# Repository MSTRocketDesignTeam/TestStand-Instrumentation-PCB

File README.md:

# Purpose
This repo will hold all of the relevant design files for the Rocket Design Team's Test Stand.

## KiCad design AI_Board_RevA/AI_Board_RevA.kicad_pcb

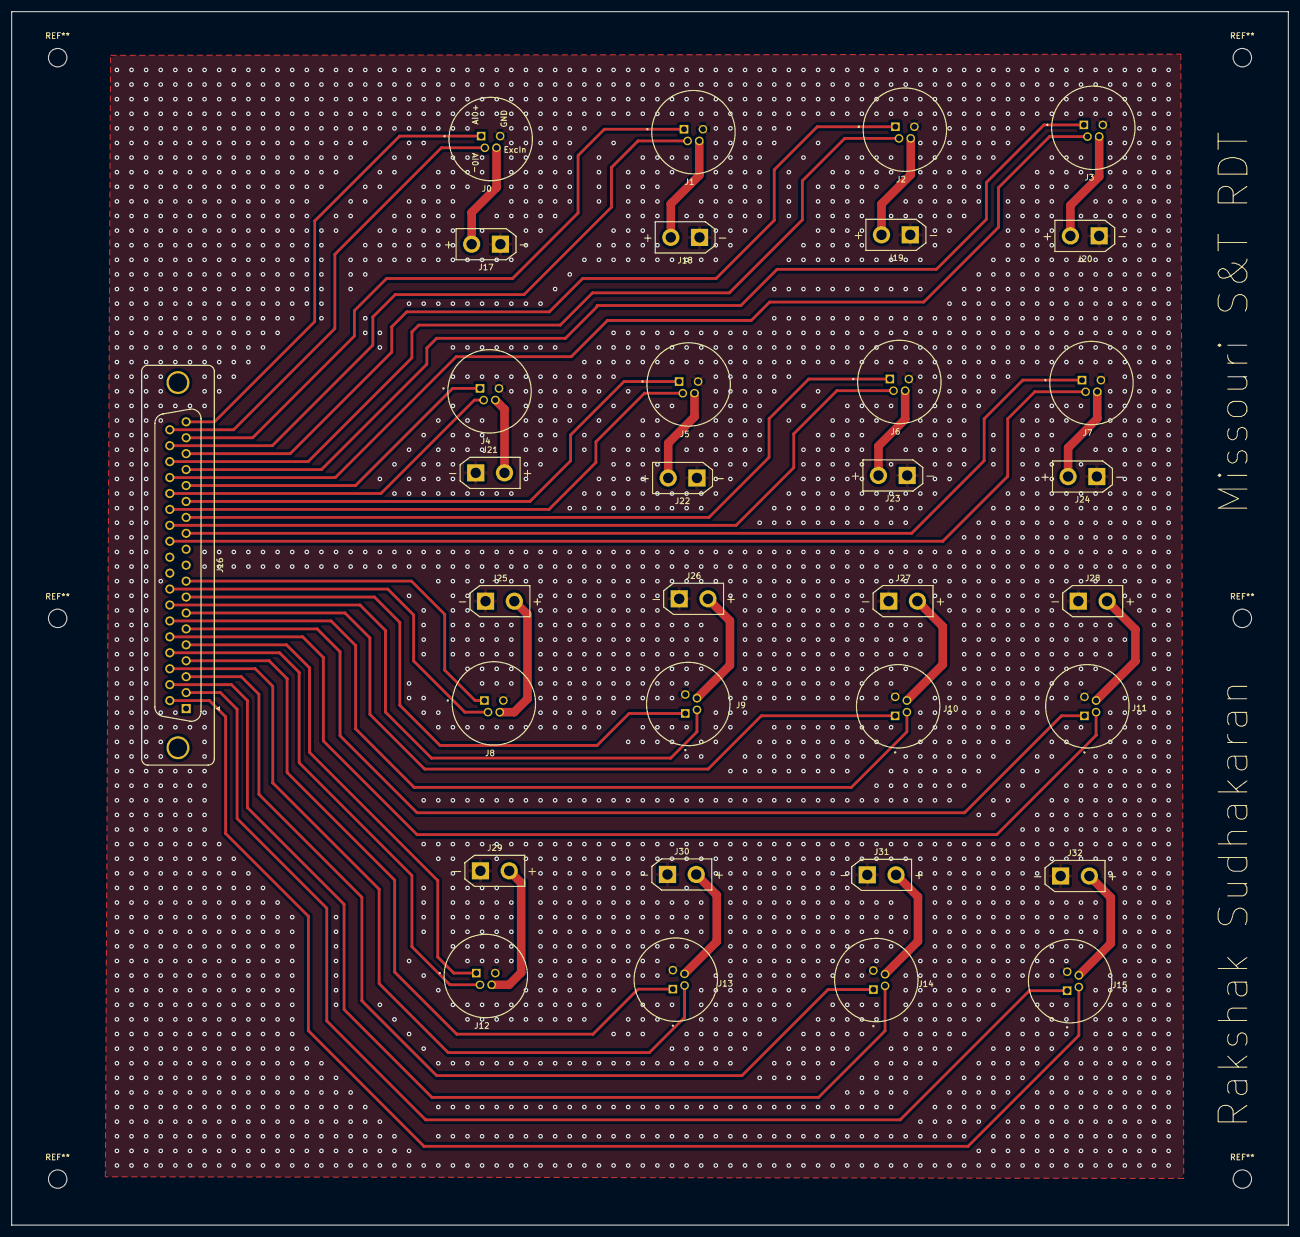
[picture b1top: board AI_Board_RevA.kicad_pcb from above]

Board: 2 copper layers, 222.0 x 211.0 mm, 33 parts (0 on the bottom side), 50 nets.

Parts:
J0, J1, J2, J3, J4, J5, J6, J7, J8, J9, J10, J11, J12, J13, J14, J15: Conn_01x04; TENSILITY_54-00278
J16: DB37_Female; DSUB-37_Female_Vertical_P2.77x2.84mm_MountingHoles
J17, J18, J19, J20, J21, J22, J23, J24, J25, J26, J27, J28, J29, J30, J31, J32: Conn_01x02; AMASS_XT30UPB-F_1x02_P5.0mm_Vertical

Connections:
/AI0+: J0.1, J16.19
/AI0-: J0.2, J16.37
/AI1+: J1.1, J16.18
/AI1-: J1.2, J16.36
/AI2+: J2.1, J16.17
/AI2-: J2.2, J16.35
/AI3+: J3.1, J16.16
/AI3-: J3.2, J16.34
/AI4+: J4.1, J16.15
/AI4-: J4.2, J16.33
/AI5+: J5.1, J16.14
/AI5-: J5.2, J16.32
/AI6+: J6.1, J16.13
/AI6-: J6.2, J16.31
/AI7+: J7.1, J16.12
/AI7-: J7.2, J16.30
/AI8+: J8.1, J16.9
/AI8-: J8.2, J16.27
/AI9+: J9.1, J16.8
/AI9-: J9.2, J16.26
/AI10+: J10.1, J16.7
/AI10-: J10.2, J16.25
/AI11+: J11.1, J16.6
/AI11-: J11.2, J16.24
/AI12+: J12.1, J16.5
/AI12-: J12.2, J16.23
/AI13+: J13.1, J16.4
/AI13-: J13.2, J16.22
/AI14+: J14.1, J16.3
/AI14-: J14.2, J16.21
/AI15+: J15.1, J16.2
/AI15-: J15.2, J16.20
/COM: J16.10, J16.11, J16.28, J16.29
GND: J0.3, J1.3, J2.3, J3.3, J4.3, J5.3, J6.3, J7.3, J8.3, J9.3, J10.3, J11.3, J12.3, J13.3, J14.3, J15.3, J17.1, J18.1, J19.1, J20.1, J21.1, J22.1, J23.1, J24.1, J25.1, J26.1, J27.1, J28.1, J29.1, J30.1, J31.1, J32.1
unnamed: J0.4, J17.2
unnamed: J1.4, J18.2
unnamed: J10.4, J27.2
unnamed: J11.4, J28.2
unnamed: J12.4, J29.2
unnamed: J13.4, J30.2
unnamed: J14.4, J31.2
unnamed: J15.4, J32.2
unnamed: J2.4, J19.2
unnamed: J3.4, J20.2
unnamed: J4.4, J21.2
unnamed: J5.4, J22.2
unnamed: J6.4, J23.2
unnamed: J7.4, J24.2
unnamed: J8.4, J25.2
unnamed: J9.4, J26.2

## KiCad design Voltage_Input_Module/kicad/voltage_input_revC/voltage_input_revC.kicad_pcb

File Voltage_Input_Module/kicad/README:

Save the main kicad project here.

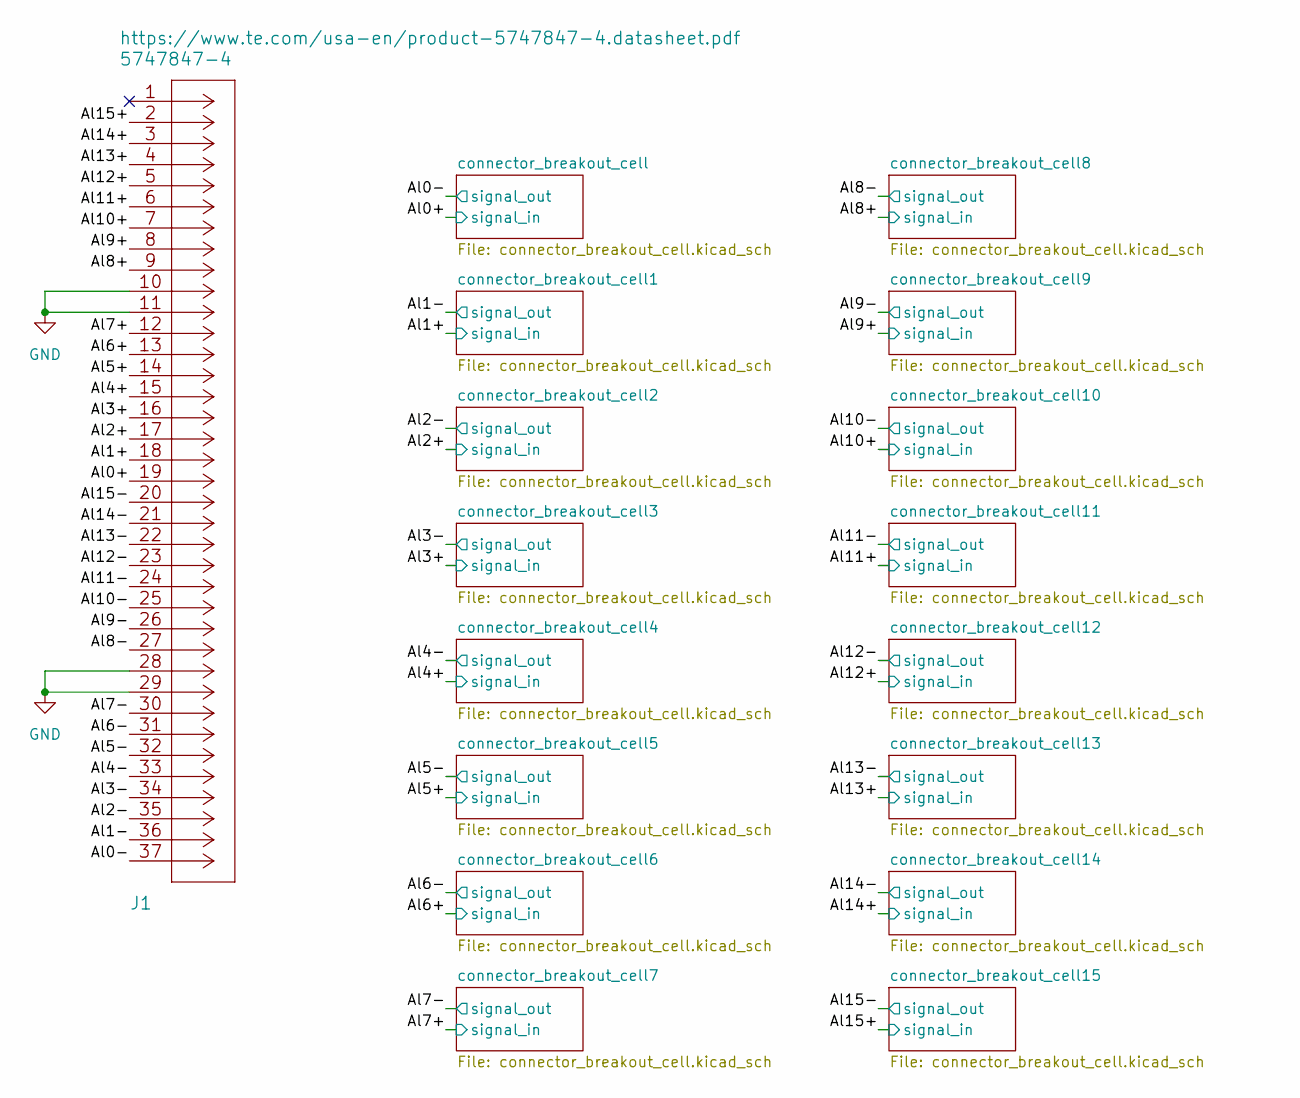
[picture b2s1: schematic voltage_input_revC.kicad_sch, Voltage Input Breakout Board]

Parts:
J1: 5747847-4

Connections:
/Al0+: J1.19; also elsewhere on the board
/Al0-: J1.37; also elsewhere on the board
/Al1+: J1.18; also elsewhere on the board
/Al1-: J1.36; also elsewhere on the board
/Al2+: J1.17; also elsewhere on the board
/Al2-: J1.35; also elsewhere on the board
/Al3+: J1.16; also elsewhere on the board
/Al3-: J1.34; also elsewhere on the board
/Al4+: J1.15; also elsewhere on the board
/Al4-: J1.33; also elsewhere on the board
/Al5+: J1.14; also elsewhere on the board
/Al5-: J1.32; also elsewhere on the board
/Al6+: J1.13; also elsewhere on the board
/Al6-: J1.31; also elsewhere on the board
/Al7+: J1.12; also elsewhere on the board
/Al7-: J1.30; also elsewhere on the board
/Al8+: J1.9; also elsewhere on the board
/Al8-: J1.27; also elsewhere on the board
/Al9+: J1.8; also elsewhere on the board
/Al9-: J1.26; also elsewhere on the board
/Al10+: J1.7; also elsewhere on the board
/Al10-: J1.25; also elsewhere on the board
/Al11+: J1.6; also elsewhere on the board
/Al11-: J1.24; also elsewhere on the board
/Al12+: J1.5; also elsewhere on the board
/Al12-: J1.23; also elsewhere on the board
/Al13+: J1.4; also elsewhere on the board
/Al13-: J1.22; also elsewhere on the board
/Al14+: J1.3; also elsewhere on the board
/Al14-: J1.21; also elsewhere on the board
/Al15+: J1.2; also elsewhere on the board
/Al15-: J1.20; also elsewhere on the board
GND: J1.10, J1.11, J1.28, J1.29; also elsewhere on the board

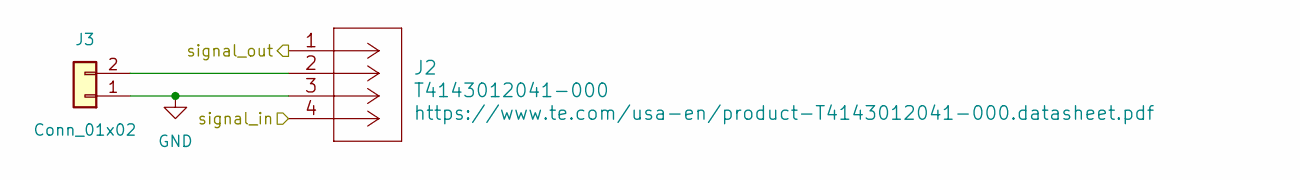
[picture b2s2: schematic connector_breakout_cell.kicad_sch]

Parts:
J2: T4143012041-000
J3: Conn_01x02; Square_Anderson_2_V_Side_By_Side

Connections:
/Al0+: J2.4; also elsewhere on the board
/Al0-: J2.1; also elsewhere on the board
GND: J2.3, J3.1; also elsewhere on the board
unnamed: J2.2, J3.2

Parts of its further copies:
J4, J6, J8, J10, J12, J14, J16, J18, J20, J22, J24, J26, J28, J30, J32: Conn_01x02; Square_Anderson_2_V_Side_By_Side
J5, J7, J9, J11, J13, J15, J17, J19, J21, J23, J25, J27, J29, J31, J33: T4143012041-000

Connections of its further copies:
/Al1+: J5.4; also elsewhere on the board
/Al1-: J5.1; also elsewhere on the board
/Al2+: J7.4; also elsewhere on the board
/Al2-: J7.1; also elsewhere on the board
/Al3+: J9.4; also elsewhere on the board
/Al3-: J9.1; also elsewhere on the board
/Al4+: J11.4; also elsewhere on the board
/Al4-: J11.1; also elsewhere on the board
/Al5+: J13.4; also elsewhere on the board
/Al5-: J13.1; also elsewhere on the board
/Al6+: J15.4; also elsewhere on the board
/Al6-: J15.1; also elsewhere on the board
/Al7+: J17.4; also elsewhere on the board
/Al7-: J17.1; also elsewhere on the board
/Al8+: J19.4; also elsewhere on the board
/Al8-: J19.1; also elsewhere on the board
/Al9+: J21.4; also elsewhere on the board
/Al9-: J21.1; also elsewhere on the board
/Al10+: J23.4; also elsewhere on the board
/Al10-: J23.1; also elsewhere on the board
/Al11+: J25.4; also elsewhere on the board
/Al11-: J25.1; also elsewhere on the board
/Al12+: J27.4; also elsewhere on the board
/Al12-: J27.1; also elsewhere on the board
/Al13+: J29.4; also elsewhere on the board
/Al13-: J29.1; also elsewhere on the board
/Al14+: J31.4; also elsewhere on the board
/Al14-: J31.1; also elsewhere on the board
/Al15+: J33.4; also elsewhere on the board
/Al15-: J33.1; also elsewhere on the board
GND: J4.1, J5.3, J6.1, J7.3, J8.1, J9.3, J10.1, J11.3, J12.1, J13.3, J14.1, J15.3, J16.1, J17.3, J18.1, J19.3, J20.1, J21.3, J22.1, J23.3, J24.1, J25.3, J26.1, J27.3, J28.1, J29.3, J30.1, J31.3, J32.1, J33.3; also elsewhere on the board
unnamed: J4.2, J5.2
unnamed: J6.2, J7.2
unnamed: J8.2, J9.2
unnamed: J10.2, J11.2
unnamed: J12.2, J13.2
unnamed: J14.2, J15.2
unnamed: J16.2, J17.2
unnamed: J18.2, J19.2
unnamed: J20.2, J21.2
unnamed: J22.2, J23.2
unnamed: J24.2, J25.2
unnamed: J26.2, J27.2
unnamed: J28.2, J29.2
unnamed: J30.2, J31.2
unnamed: J32.2, J33.2

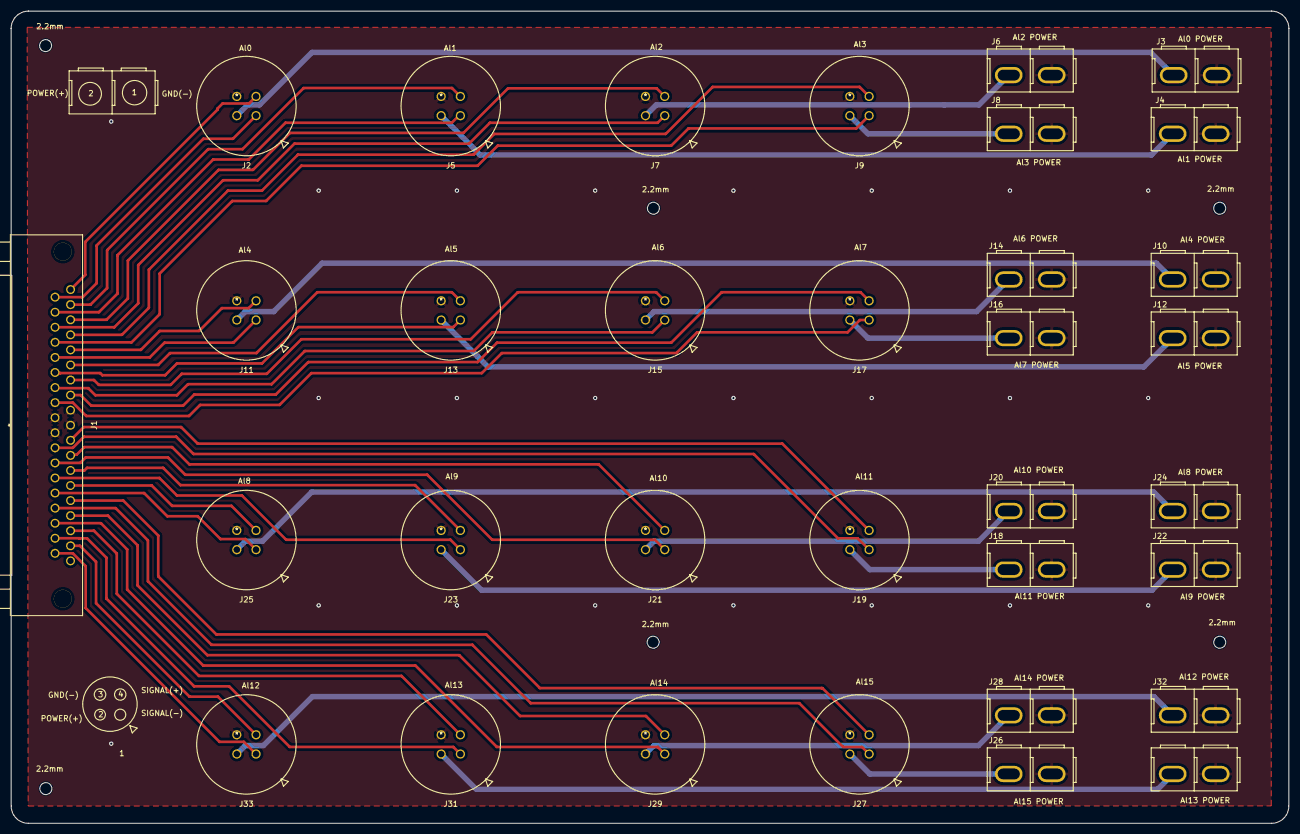
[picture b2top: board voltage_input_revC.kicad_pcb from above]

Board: 2 copper layers, 234.7 x 149.2 mm, 33 parts (0 on the bottom side), 49 nets.

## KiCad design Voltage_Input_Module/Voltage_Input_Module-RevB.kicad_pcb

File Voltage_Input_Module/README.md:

# Voltage Input Module
This module will handle handle the DAQ's NI-9202 Analog Inputs. It will provide power to various sensors and connect signal lines to the appropriate DAQ inputs. Any unused pins will be made available in headers or test points for future expandabilty.

## Directory Structure
```mermaid
flowchart TD
1{{Voltage_Input_Module/}} --- 2(kicad/)
1 --- 3(datasheets/)
2 --- 4(hierarchical_sheets/)
2 --- 5(libraries/)
5 --- 6(["*.pretty/"])
4 --- 7([*.kicad_sch])
2 --- 8([*.kicad_pro])
3 --- 9([*.pdf])
5 --- 10([*.lib])
```

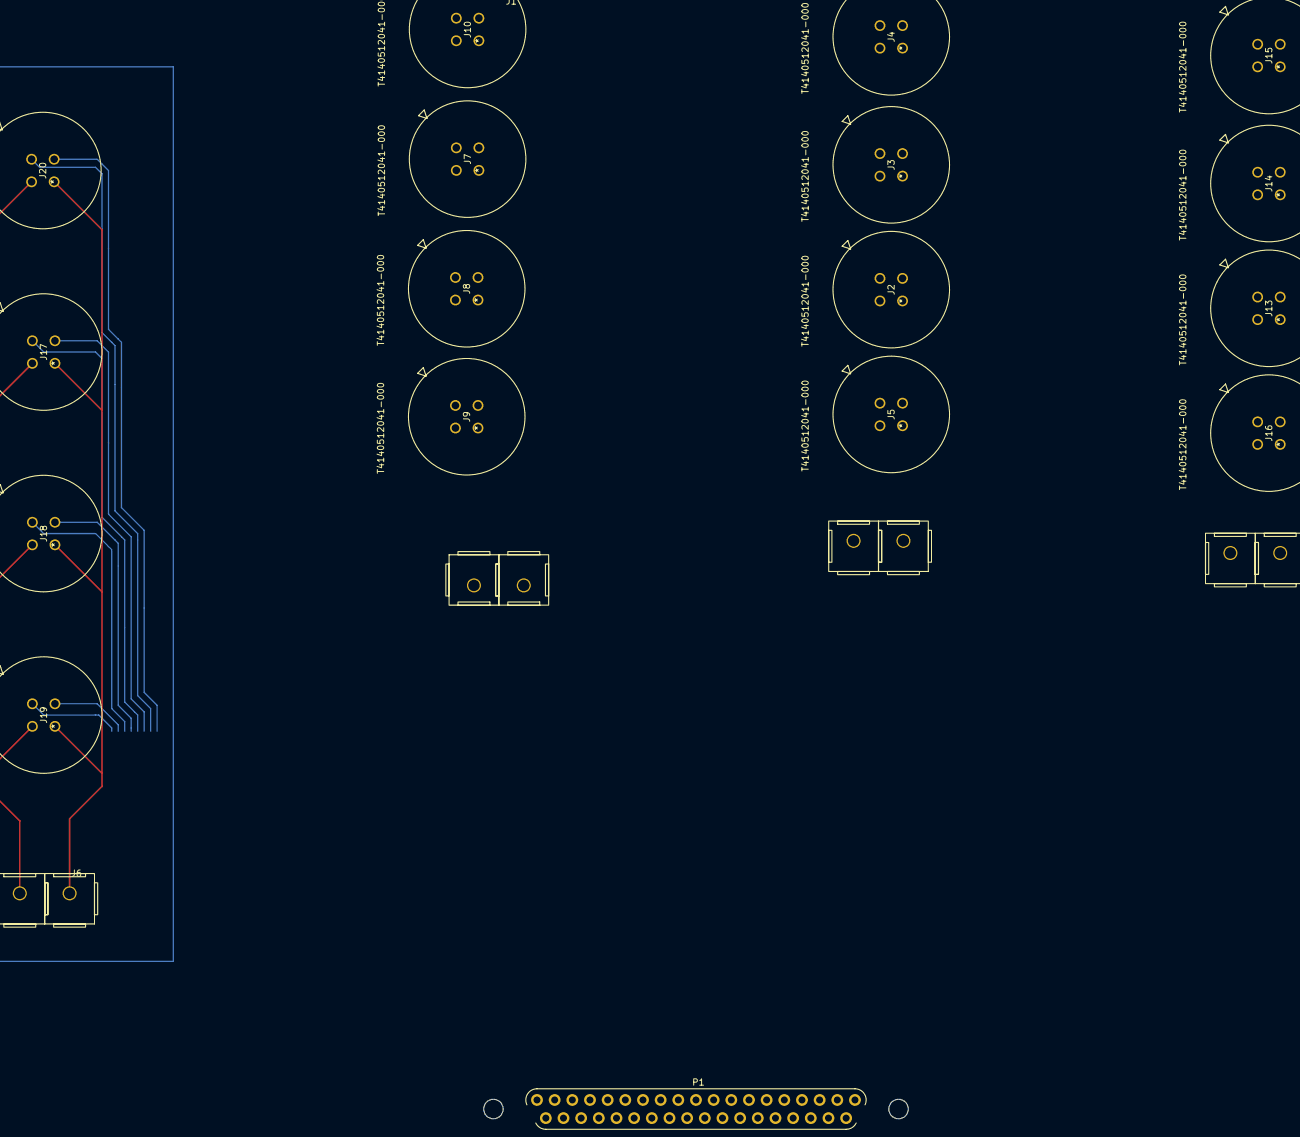
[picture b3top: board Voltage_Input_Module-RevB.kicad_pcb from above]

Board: 2 copper layers, 21 parts (0 on the bottom side), 37 nets.

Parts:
J1, J6, J11, J12: Conn_01x02; 2x_Anderson_Powerpole-25A-S-H-G11
J2, J3, J4, J5, J7, J8, J9, J10, J13, J14, J15, J16, J17, J18, J19, J20: T4140512041-000
P1: 182-037-113R541; 182-037-113R451

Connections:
/4x_4_pin_connector1/power: J11.2, J13.2, J14.2, J15.2, J16.2
/4x_4_pin_connector2/power: J1.2, J7.2, J8.2, J9.2, J10.2
/4x_4_pin_connector3/power: J6.2, J17.2, J18.2, J19.2, J20.2
/4x_4_pin_connector/power: J2.2, J3.2, J4.2, J5.2, J12.2
/AI0+: J16.1, P1.1
/AI0-: J16.4, P1.20
/AI1+: J13.1, P1.2
/AI1-: J13.4, P1.21
/AI2+: J14.1, P1.3
/AI2-: J14.4, P1.22
/AI3+: J15.1, P1.4
/AI3-: J15.4, P1.23
/AI4+: J5.1, P1.5
/AI4-: J5.4, P1.24
/AI5+: J2.1, P1.6
/AI5-: J2.4, P1.25
/AI6+: J3.1, P1.7
/AI6-: J3.4, P1.26
/AI7+: J4.1, P1.8
/AI7-: J4.4, P1.27
/AI8+: J10.4, P1.11
/AI8-: J10.1, P1.30
/AI9+: J7.4, P1.12
/AI9-: J7.1, P1.31
/AI10+: J8.4, P1.13
/AI10-: J8.1, P1.32
/AI11+: J9.4, P1.14
/AI11-: J9.1, P1.33
/AI12+: J20.4, P1.15
/AI12-: J20.1, P1.34
/AI13+: J17.4, P1.16
/AI13-: J17.1, P1.35
/AI14+: J18.4, P1.17
/AI14-: J18.1, P1.36
/AI15+: J19.4, P1.18
/AI15-: J19.1, P1.37
GND: J1.1, J2.3, J3.3, J4.3, J5.3, J6.1, J7.3, J8.3, J9.3, J10.3, J11.1, J12.1, J13.3, J14.3, J15.3, J16.3, J17.3, J18.3, J19.3, J20.3, P1.9, P1.10, P1.28, P1.29

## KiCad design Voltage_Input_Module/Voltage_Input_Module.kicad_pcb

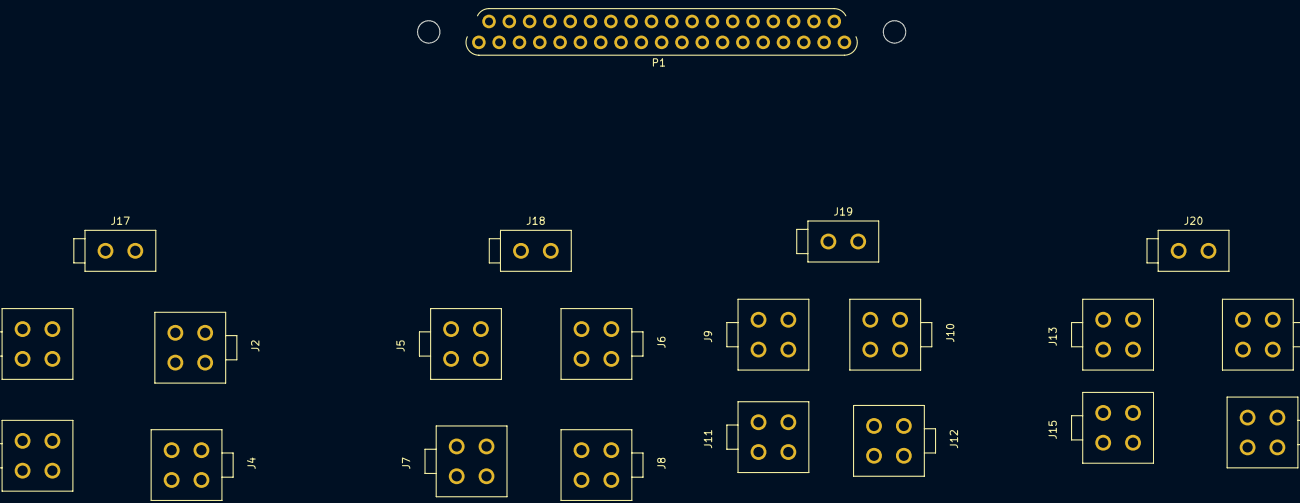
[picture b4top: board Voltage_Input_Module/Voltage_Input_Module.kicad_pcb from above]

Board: 2 copper layers, 21 parts (0 on the bottom side), 24 nets, no tracks yet.

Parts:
J1, J2, J3, J4, J5, J6, J7, J8, J9, J10, J11, J12, J13, J14, J15, J16: 0039281043
J17, J18, J19, J20: 0039281023
P1: 182-037-113R541; 182-037-113R451

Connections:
unnamed: J1.1, J2.1, J3.1, J4.1, J17.1
unnamed: J1.2, J2.2, J3.2, J4.2, J17.2, P1.9, P1.20, P1.21, P1.22, P1.23
unnamed: J1.3, P1.1
unnamed: J2.3, P1.2
unnamed: J3.3, P1.3
unnamed: J4.3, P1.4
unnamed: J5.3, P1.5
unnamed: J6.3, P1.6
unnamed: J7.3, P1.7
unnamed: J8.3, P1.8
unnamed: J9.3, P1.11
unnamed: J9.1, J10.1, J11.1, J12.1, J19.1
unnamed: J9.2, J10.2, J11.2, J12.2, J19.2, P1.10, P1.30, P1.31, P1.32, P1.33
unnamed: J10.3, P1.12
unnamed: J11.3, P1.13
unnamed: J12.3, P1.14
unnamed: J13.1, J14.1, J15.1, J16.1, J20.1
unnamed: J13.2, J14.2, J15.2, J16.2, J20.2, P1.29, P1.34, P1.35, P1.36, P1.37
unnamed: J13.3, P1.15
unnamed: J14.3, P1.16
unnamed: J15.3, P1.17
unnamed: J16.3, P1.18
unnamed: J5.1, J6.1, J7.1, J8.1, J18.1
unnamed: J5.2, J6.2, J7.2, J8.2, J18.2, P1.24, P1.25, P1.26, P1.27, P1.28

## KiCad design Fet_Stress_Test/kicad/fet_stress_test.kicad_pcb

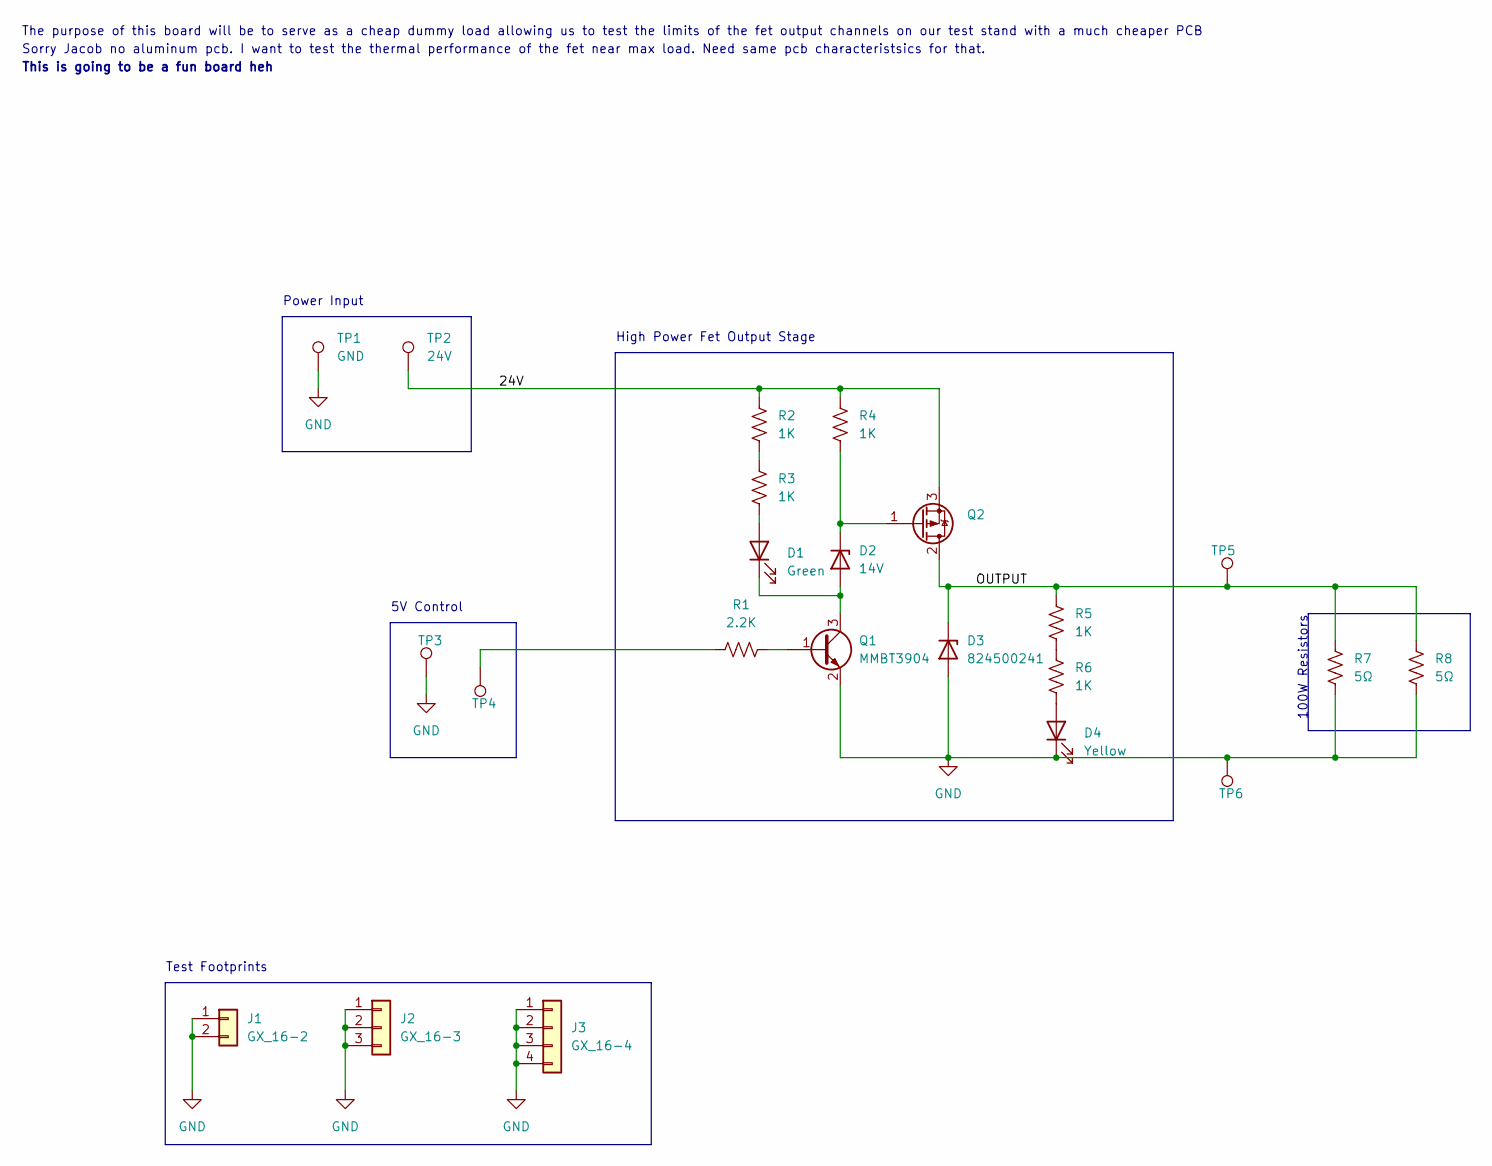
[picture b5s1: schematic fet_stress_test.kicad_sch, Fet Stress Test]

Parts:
D1: Green; LED_D5.0mm
D2: 14V; D_SOD-123
D3: 824500241; D_SMA
D4: Yellow; LED_D5.0mm
J1: GX_16-2
J2: GX_16-3
J3: GX_16-4
Q1: MMBT3904; SOT-23
Q2: TO-220F-3_Horizontal_TabDown_SMD_PAD
R1: 2.2K; R_0603_1608Metric_Pad0.98x0.95mm_HandSolder
R2, R3, R4, R5, R6: 1K; R_0603_1608Metric_Pad0.98x0.95mm_HandSolder
R7, R8: 5Ω; TO-247-2_Horizontal_TabDown
TP1: GND; 15x15mm_pad
TP2: 24V; 15x15mm_pad
TP3, TP4, TP5, TP6: TestPoint; TestPoint_THTPad_D1.5mm_Drill0.7mm

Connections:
/24V: Q2.3 (S), R2.1, R4.1, TP2.1
/OUTPUT: D3.1 (K), Q2.2 (D), R5.1, R7.1, R8.2, TP5.1
GND: D3.2 (A), D4.1 (K), J1.1, J1.2, J2.1, J2.2, J2.3, J3.1, J3.2, J3.3, J3.4, Q1.2 (E), R7.2, R8.1, TP1.1, TP3.1, TP6.1
unnamed: D1.1 (K), D2.2 (A), Q1.3 (C)
unnamed: D1.2 (A), R3.2
unnamed: D2.1 (K), Q2.1 (G), R4.2
unnamed: D4.2 (A), R6.2
unnamed: Q1.1 (B), R1.1
unnamed: R1.2, TP4.1
unnamed: R2.2, R3.1
unnamed: R5.2, R6.1

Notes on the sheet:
High Power Fet Output Stage
Test Footprints
The purpose of this board will be to serve as a cheap dummy load allowing us to test the limits of the fet output channels on our test stand with a much cheaper PCB
This is going to be a fun board heh
100W Resistors
Power Input
5V Control
Sorry Jacob no aluminum pcb. I want to test the thermal performance of the fet near max load. Need same pcb characteristsics for that.

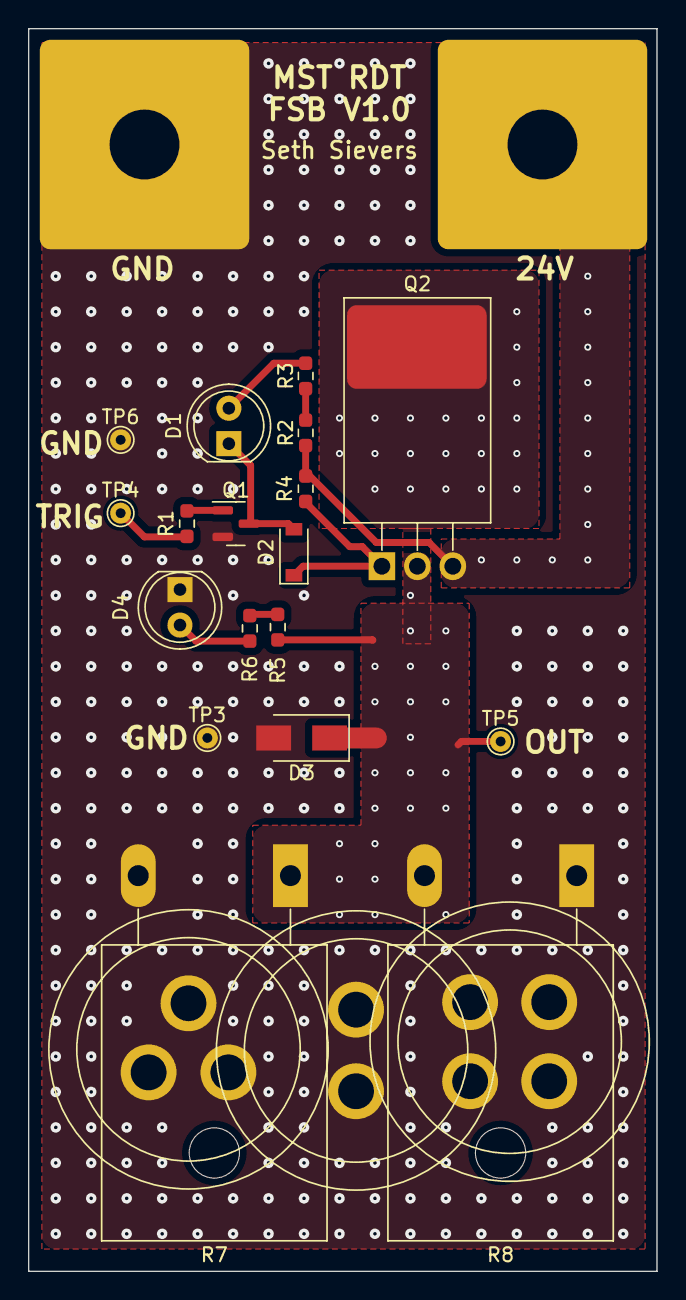
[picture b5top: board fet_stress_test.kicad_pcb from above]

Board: 2 copper layers, 45.0 x 89.0 mm, 23 parts (0 on the bottom side), 11 nets.

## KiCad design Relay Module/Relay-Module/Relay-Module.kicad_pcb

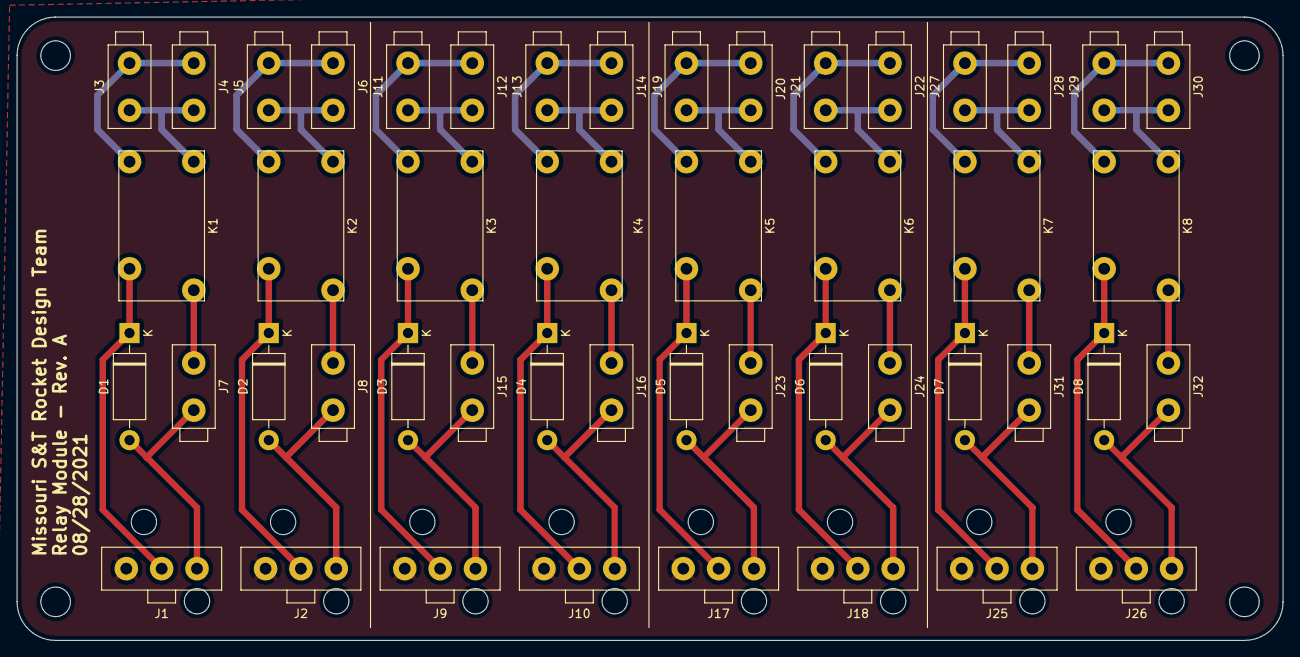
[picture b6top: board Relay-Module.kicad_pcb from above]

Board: 2 copper layers, 150.1 x 73.9 mm, 48 parts (0 on the bottom side), 41 nets.

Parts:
D1, D2, D3, D4, D5, D6, D7, D8: SB5100-T; D_DO-15_P12.70mm_Horizontal
J1, J2, J9, J10, J17, J18, J25, J26: 0039301039
J3, J4, J5, J6, J7, J8, J11, J12, J13, J14, J15, J16, J19, J20, J21, J22, J23, J24, J27, J28, J29, J30, J31, J32: 0039281023
K1, K2, K3, K4, K5, K6, K7, K8: T77S1D3-05

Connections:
GND: J1.3, J2.3, J9.3, J10.3, J17.3, J18.3, J25.3, J26.3
unnamed: D1.1, J1.2, K1.4
unnamed: D1.2, J1.1, J7.2
unnamed: D2.1, J2.2, K2.4
unnamed: D2.2, J2.1, J8.2
unnamed: D3.1, J9.2, K3.4
unnamed: D3.2, J9.1, J15.2
unnamed: D4.1, J10.2, K4.4
unnamed: D4.2, J10.1, J16.2
unnamed: D5.1, J17.2, K5.4
unnamed: D5.2, J17.1, J23.2
unnamed: D6.1, J18.2, K6.4
unnamed: D6.2, J18.1, J24.2
unnamed: D7.1, J25.2, K7.4
unnamed: D7.2, J25.1, J31.2
unnamed: D8.1, J26.2, K8.4
unnamed: D8.2, J26.1, J32.2
unnamed: J3.1, J4.1, K1.1
unnamed: J3.2, J4.2, K1.2
unnamed: J5.1, J6.1, K2.1
unnamed: J5.2, J6.2, K2.2
unnamed: J7.1, K1.3
unnamed: J8.1, K2.3
unnamed: J11.1, J12.1, K3.1
unnamed: J11.2, J12.2, K3.2
unnamed: J13.1, J14.1, K4.1
unnamed: J13.2, J14.2, K4.2
unnamed: J15.1, K3.3
unnamed: J16.1, K4.3
unnamed: J19.1, J20.1, K5.1
unnamed: J19.2, J20.2, K5.2
unnamed: J21.1, J22.1, K6.1
unnamed: J21.2, J22.2, K6.2
unnamed: J23.1, K5.3
unnamed: J24.1, K6.3
unnamed: J27.1, J28.1, K7.1
unnamed: J27.2, J28.2, K7.2
unnamed: J29.1, J30.1, K8.1
unnamed: J29.2, J30.2, K8.2
unnamed: J31.1, K7.3
unnamed: J32.1, K8.3

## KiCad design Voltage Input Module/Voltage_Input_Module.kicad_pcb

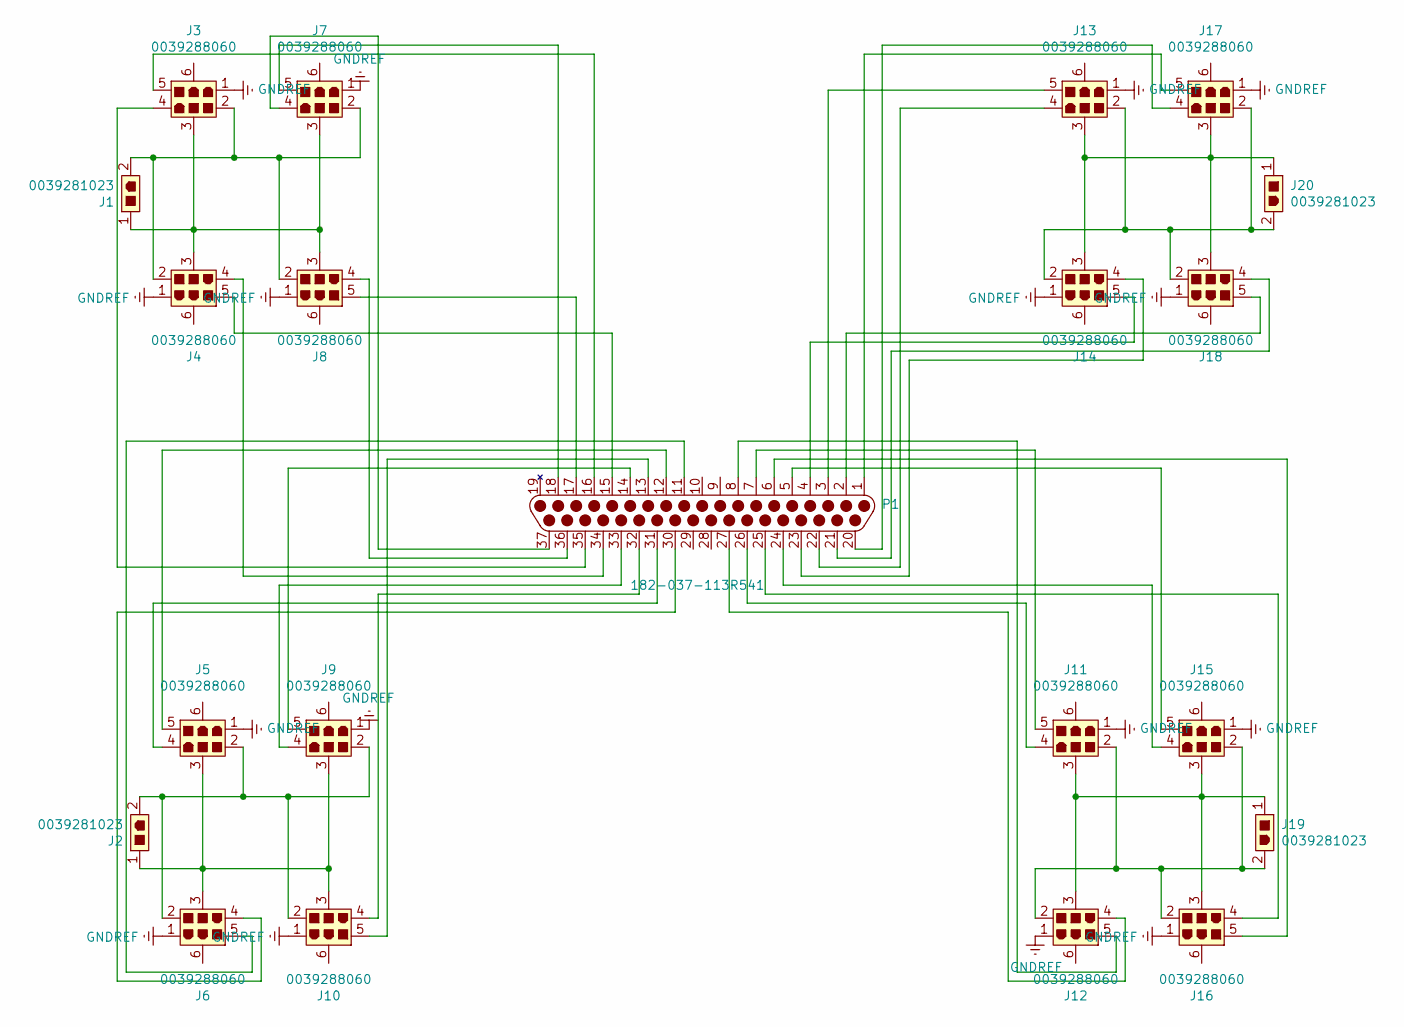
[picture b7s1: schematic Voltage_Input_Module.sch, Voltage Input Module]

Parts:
J1, J2, J19, J20: 0039281023; MPN 0039281043; Digi-Key_PN WM3801-ND
J3, J4, J5, J6, J7, J8, J9, J10, J11, J12, J13, J14, J15, J16, J17, J18: 0039288060; MPN 0039281043; Digi-Key_PN WM3801-ND
P1: 182-037-113R541; 182-037-113R451

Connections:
GNDREF: J3.1, J4.1, J5.1, J6.1, J7.1, J8.1, J9.1, J10.1, J11.1, J12.1, J13.1, J14.1, J15.1, J16.1, J17.1, J18.1
unnamed: J1.1, J3.3, J4.3, J7.3, J8.3
unnamed: J1.2, J3.2, J4.2, J7.2, J8.2
unnamed: J3.4, P1.35
unnamed: J3.5, P1.16
unnamed: J4.4, P1.34
unnamed: J4.5, P1.15
unnamed: J5.4, P1.31
unnamed: J5.5, P1.12
unnamed: J6.4, P1.30
unnamed: J6.5, P1.11
unnamed: J7.4, P1.37
unnamed: J7.5, P1.18
unnamed: J8.4, P1.36
unnamed: J8.5, P1.17
unnamed: J9.4, P1.33
unnamed: J9.5, P1.14
unnamed: J2.2, J5.2, J6.2, J9.2, J10.2
unnamed: J2.1, J5.3, J6.3, J9.3, J10.3
unnamed: J10.4, P1.32
unnamed: J10.5, P1.13
unnamed: J11.2, J12.2, J15.2, J16.2, J19.2
unnamed: J11.3, J12.3, J15.3, J16.3, J19.1
unnamed: J11.4, P1.26
unnamed: J11.5, P1.7
unnamed: J12.4, P1.27
unnamed: J12.5, P1.8
unnamed: J13.2, J14.2, J17.2, J18.2, J20.2
unnamed: J13.3, J14.3, J17.3, J18.3, J20.1
unnamed: J13.4, P1.22
unnamed: J13.5, P1.3
unnamed: J14.4, P1.23
unnamed: J14.5, P1.4
unnamed: J15.4, P1.24
unnamed: J15.5, P1.5
unnamed: J16.4, P1.25
unnamed: J16.5, P1.6
unnamed: J17.4, P1.20
unnamed: J17.5, P1.1
unnamed: J18.4, P1.21
unnamed: J18.5, P1.2

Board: 2 copper layers, 21 parts (0 on the bottom side), 41 nets, no tracks yet.

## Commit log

2021-08-10 Revised mini-fit schematics and footprints and created initial PCB layout
2021-08-28 Relay Module Completion
    Relay module is complete, this includes the schematic, custom symbols and footprints, and the pcb itself.
2021-08-28 Relay module update and trigger module creation
2021-09-30 Create LICENSE
2022-01-22 Updated Files
    Module updates and general fixes
2022-07-14 changes to board
2022-07-14 Restructured
2022-07-15 Started DOM schematic and made some footprints
2022-07-15 Progress on fet output channel
2022-07-16 Uploading Evil Schemes
2022-07-16 file sync
2022-07-17 started work routing fet stress
2022-07-17 Finsihed stress test pcb and generated gerbes
2022-08-02 Finalized footprints and regenerated gerbers, added BOM
2022-08-02 removed uneeded
2022-08-02 added readme
2022-08-02 small pcb update
2022-08-03 tweak BOM wording
2023-03-13 moved files to make room
2023-03-13 readme
2023-03-13 adding directory
2023-03-13 fixed directory /
2023-03-13 file upload
2023-03-13 Are these the right files?
2023-03-13 .gitignore added
2023-03-24 File updates
    Added petty for footprints. 3d for 3d objects. Updated folders with correct footprints. Deleted old files to clean up formatting. basically restarted.
2023-03-24 Completed schematic file. Added hierarchical sheet for connector cells. Linked symbols to footprints, and footprints to 3d models.
2023-03-24 Untangled birds nest. Laid out footprints for PCB. Added ground connection to connector breakout cell. Need to make traces, making sure they're wide enough.
2023-03-25 Started work on trances. Added ground plane, need mounting positions, finish traces, rework/do powerpole connections.
2023-03-25 Finished traces, Implemented footprints and 3d models for powerpole connections. Added mounting holes and edge cuts. Need to implement silk screen callouts for sensors.
2023-03-27 Further reworked traces. Implemented spaces for grounding.
2023-03-28 Finalized traces. Finalized edge cuts. Finalized ground plane. Added vias. Added mounting holes. Added annotations to PCB.
2023-03-28 Moved footprints off of vias
2023-03-28 creating new relay board project
2023-03-28 file structure change
2023-03-28 these files are being difficult
2023-03-28 finished voltage selector switch
2023-10-11 Add files via upload
    Initial commit
2023-10-11 Delete Relay_Board_RevA.kicad_pro
    Improper file format
2023-10-12 Initial commit of Analog Input Board
2023-10-15 Initial commit for LabVIEW Code
2023-11-23 Penultimate draft

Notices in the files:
parts and their libraries:
Copyright 2021 Accelerated Designs. All rights reserved.
